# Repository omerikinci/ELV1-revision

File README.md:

# ELV1 Revision

Standalone KiCad hardware repository for the ELV1 revision project.

Main project file:

```text
hardware/ELV1-revision/ELV1 revision.kicad_pro
```

Local project libraries are kept under:

```text
hardware/libraries
```

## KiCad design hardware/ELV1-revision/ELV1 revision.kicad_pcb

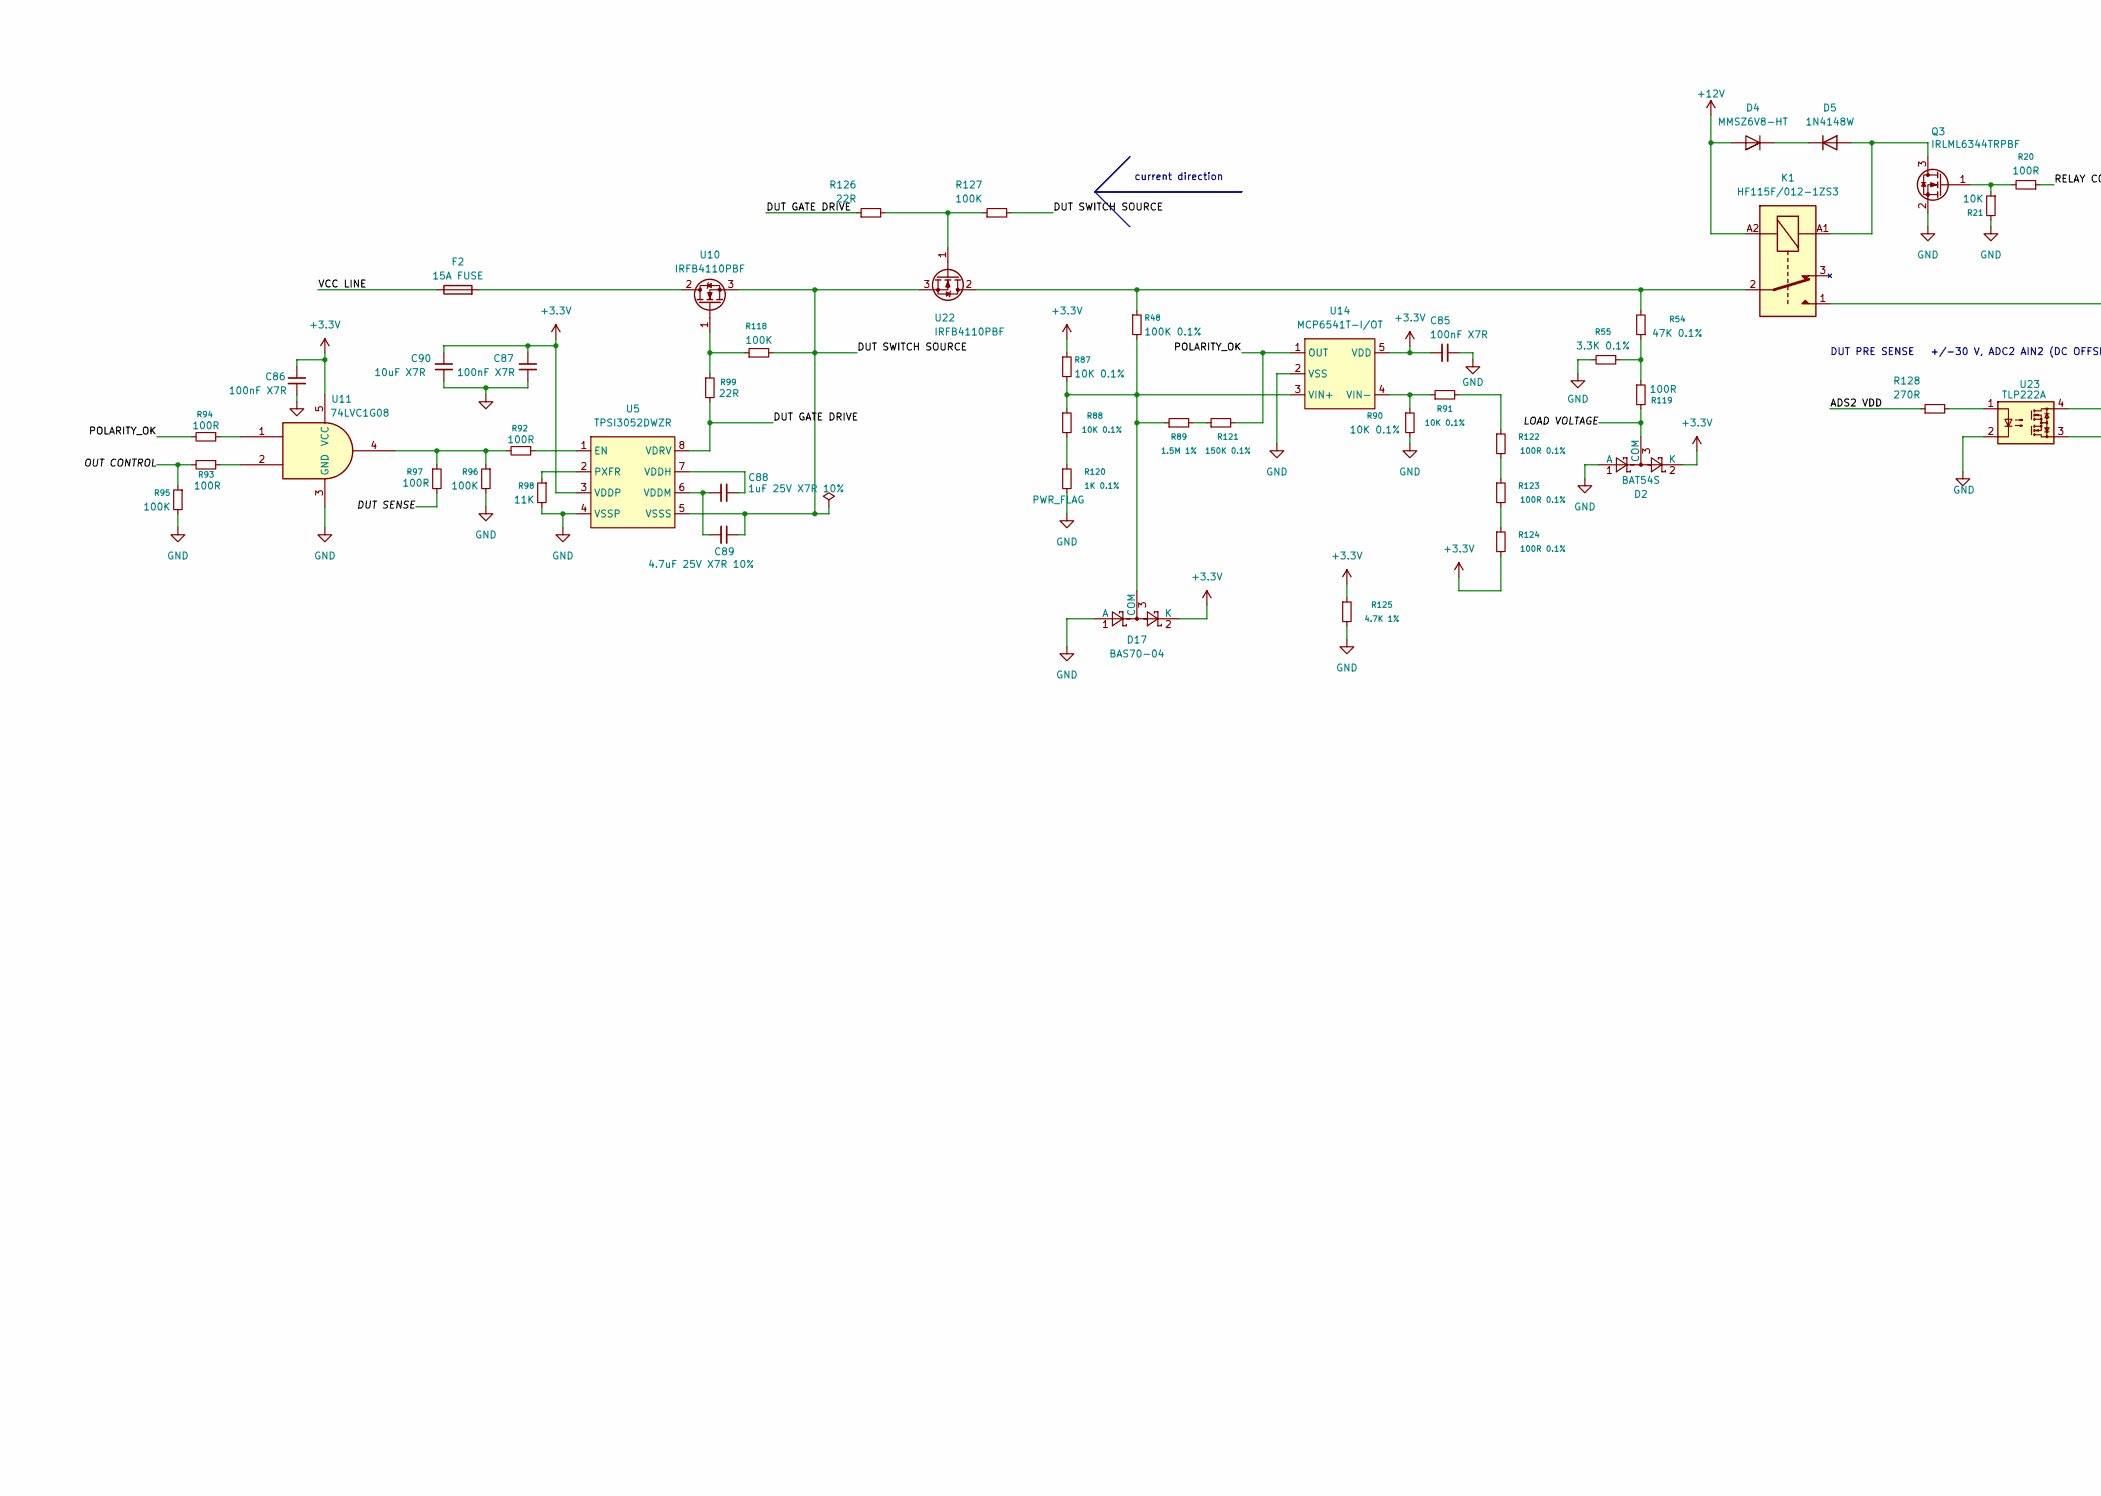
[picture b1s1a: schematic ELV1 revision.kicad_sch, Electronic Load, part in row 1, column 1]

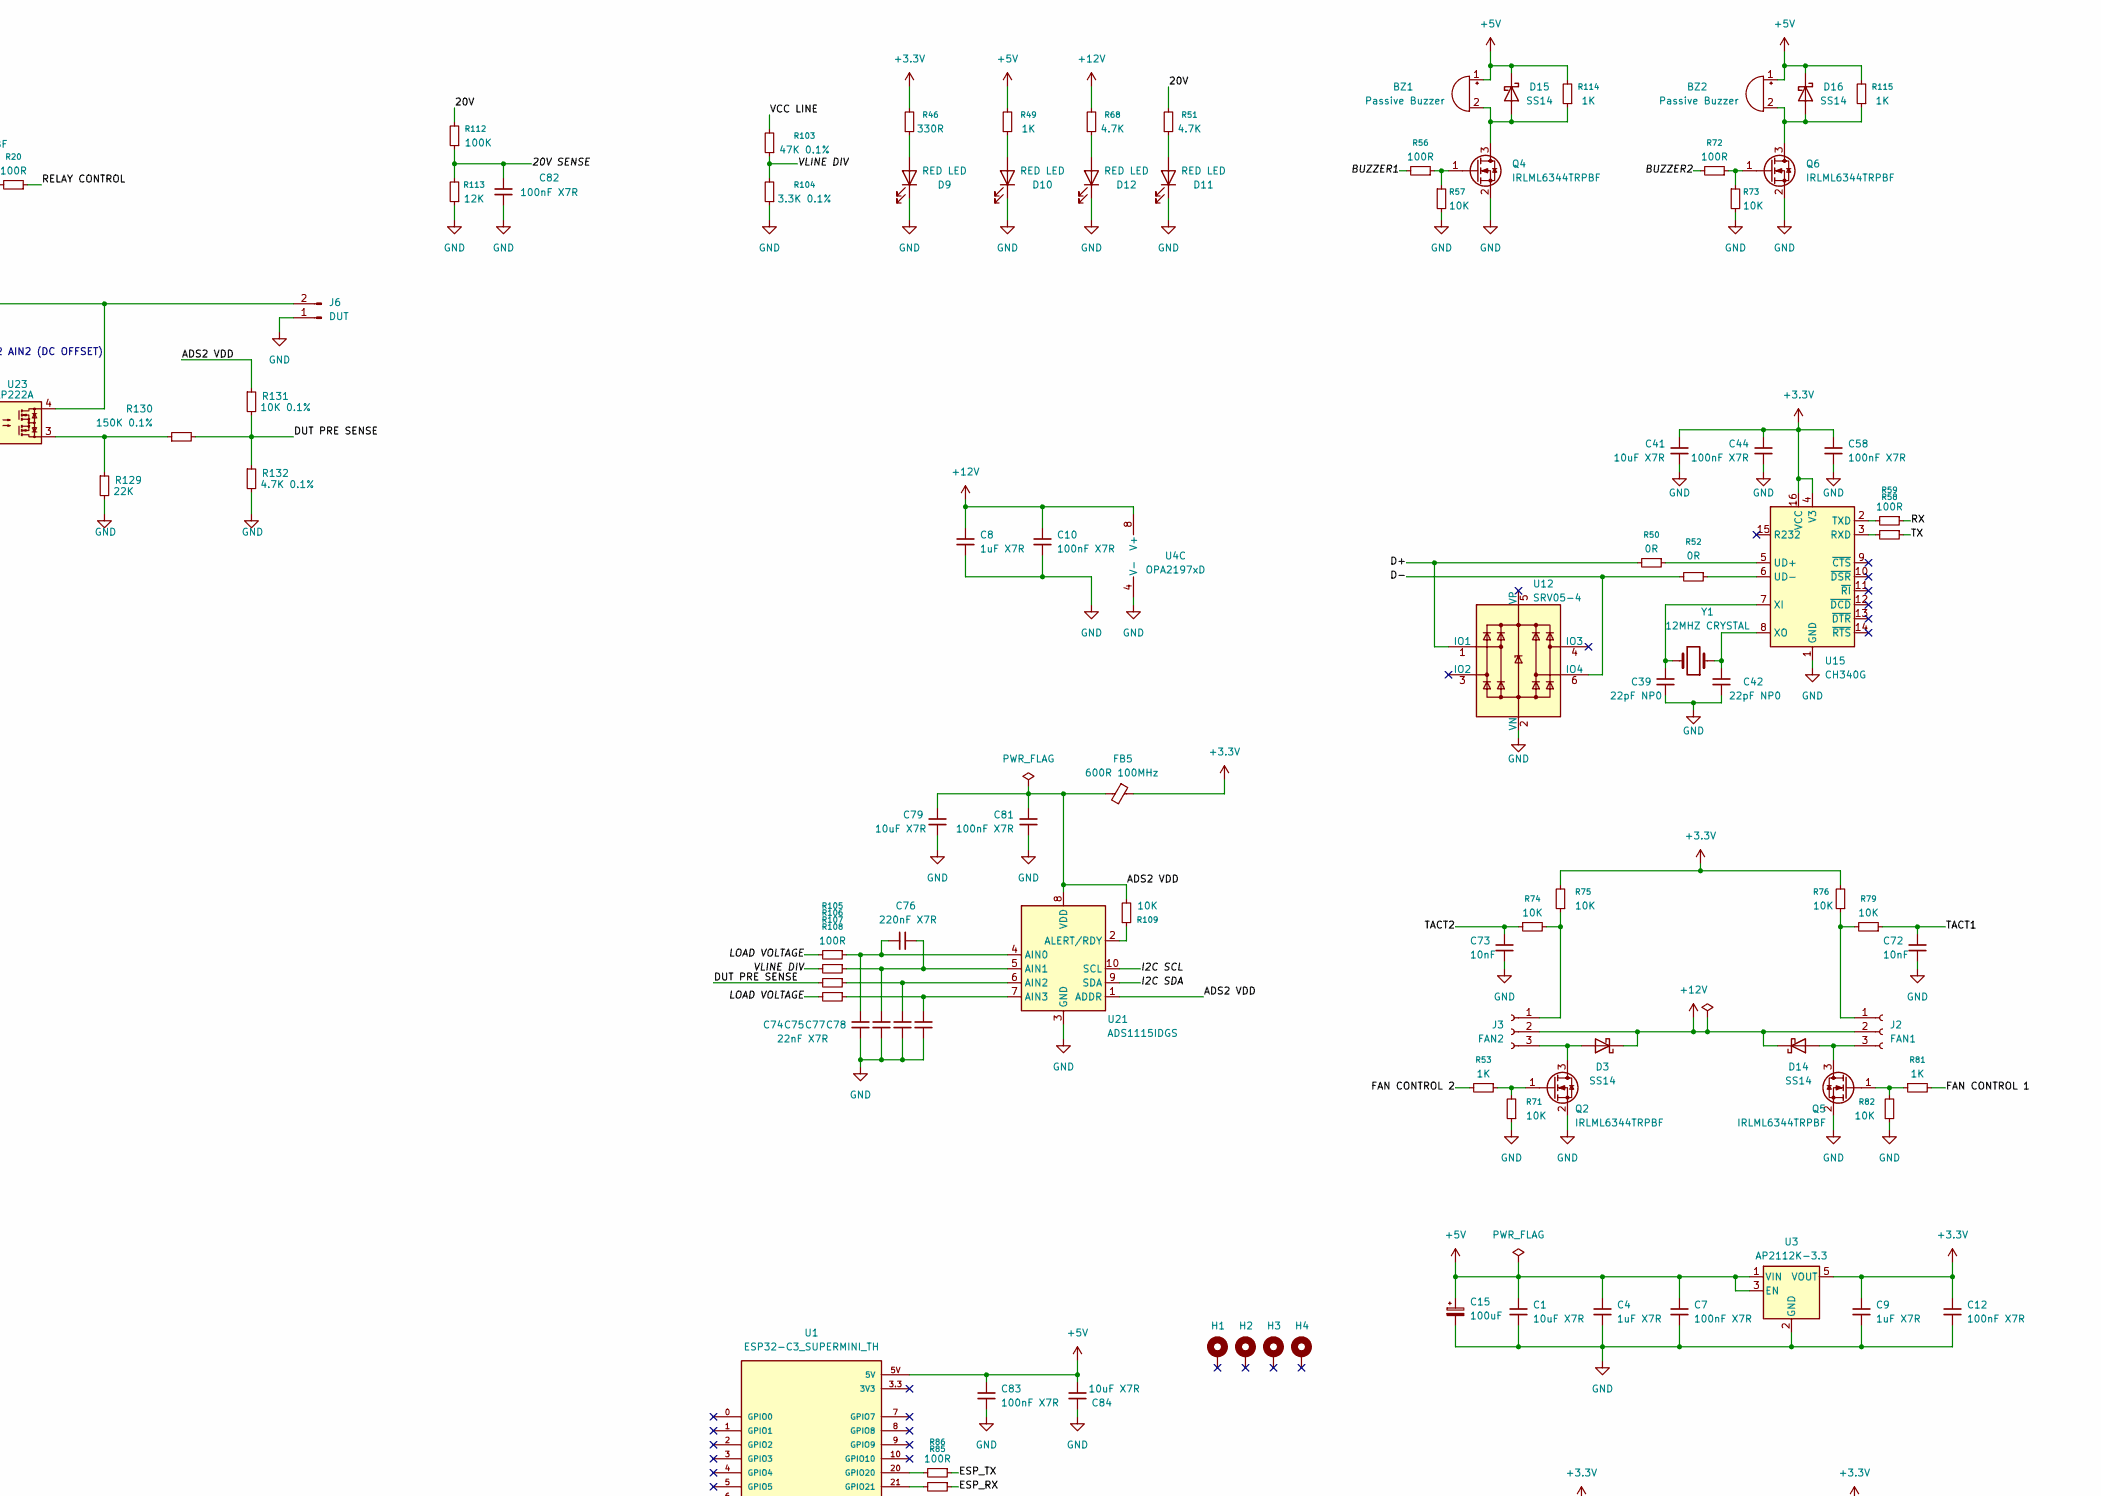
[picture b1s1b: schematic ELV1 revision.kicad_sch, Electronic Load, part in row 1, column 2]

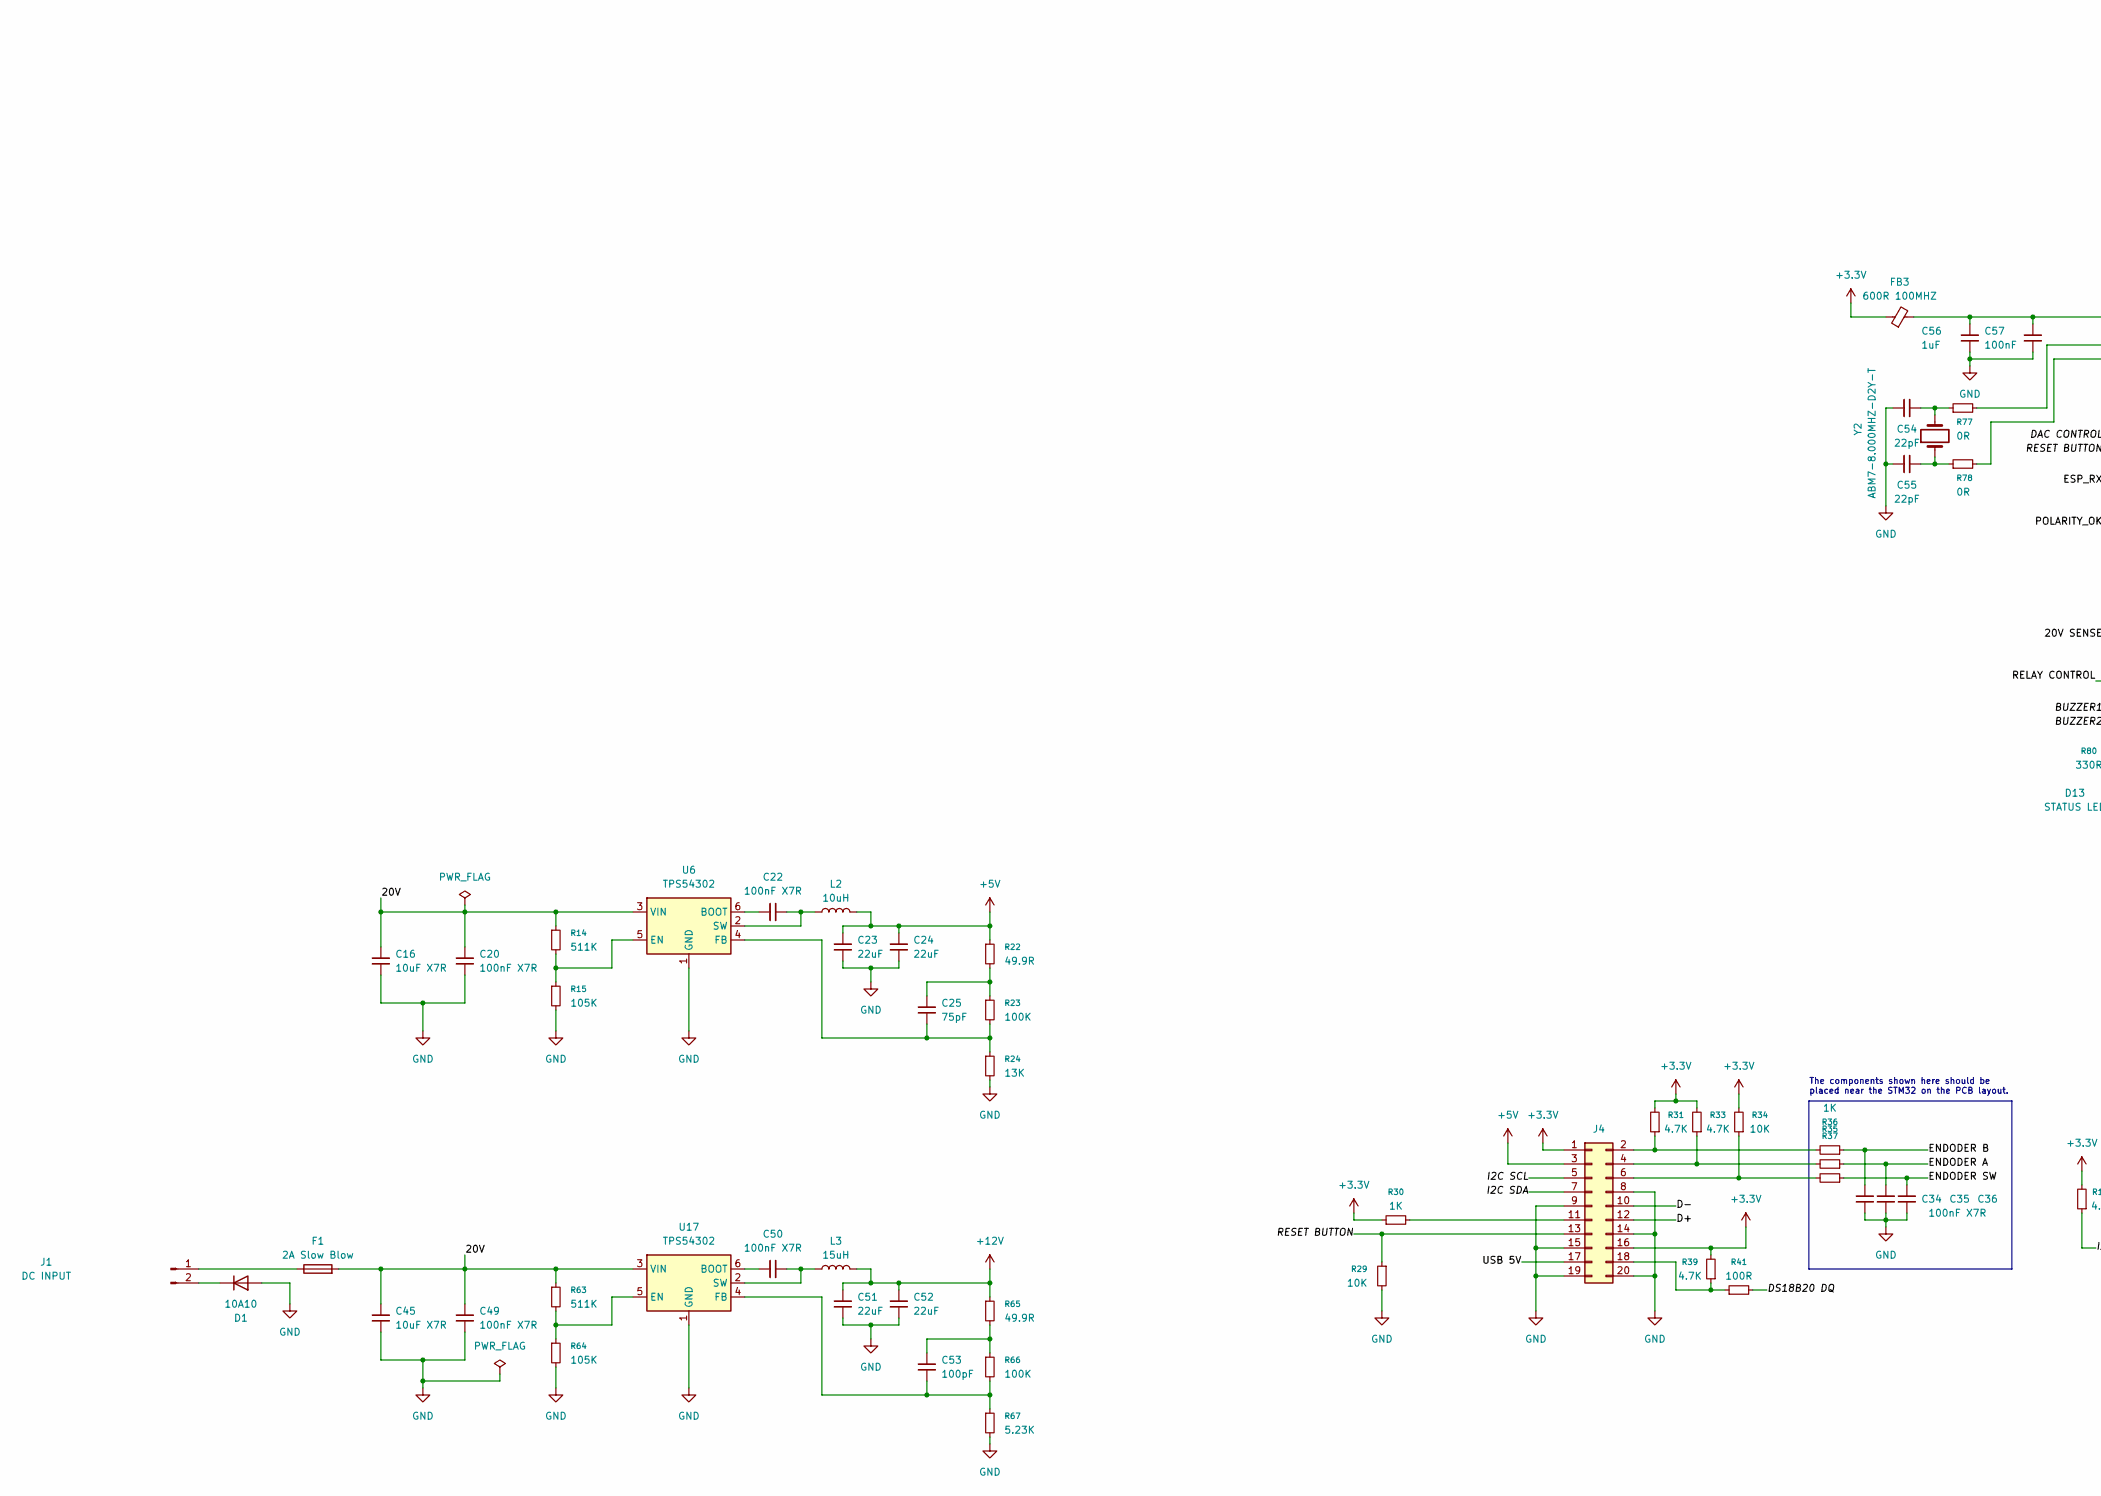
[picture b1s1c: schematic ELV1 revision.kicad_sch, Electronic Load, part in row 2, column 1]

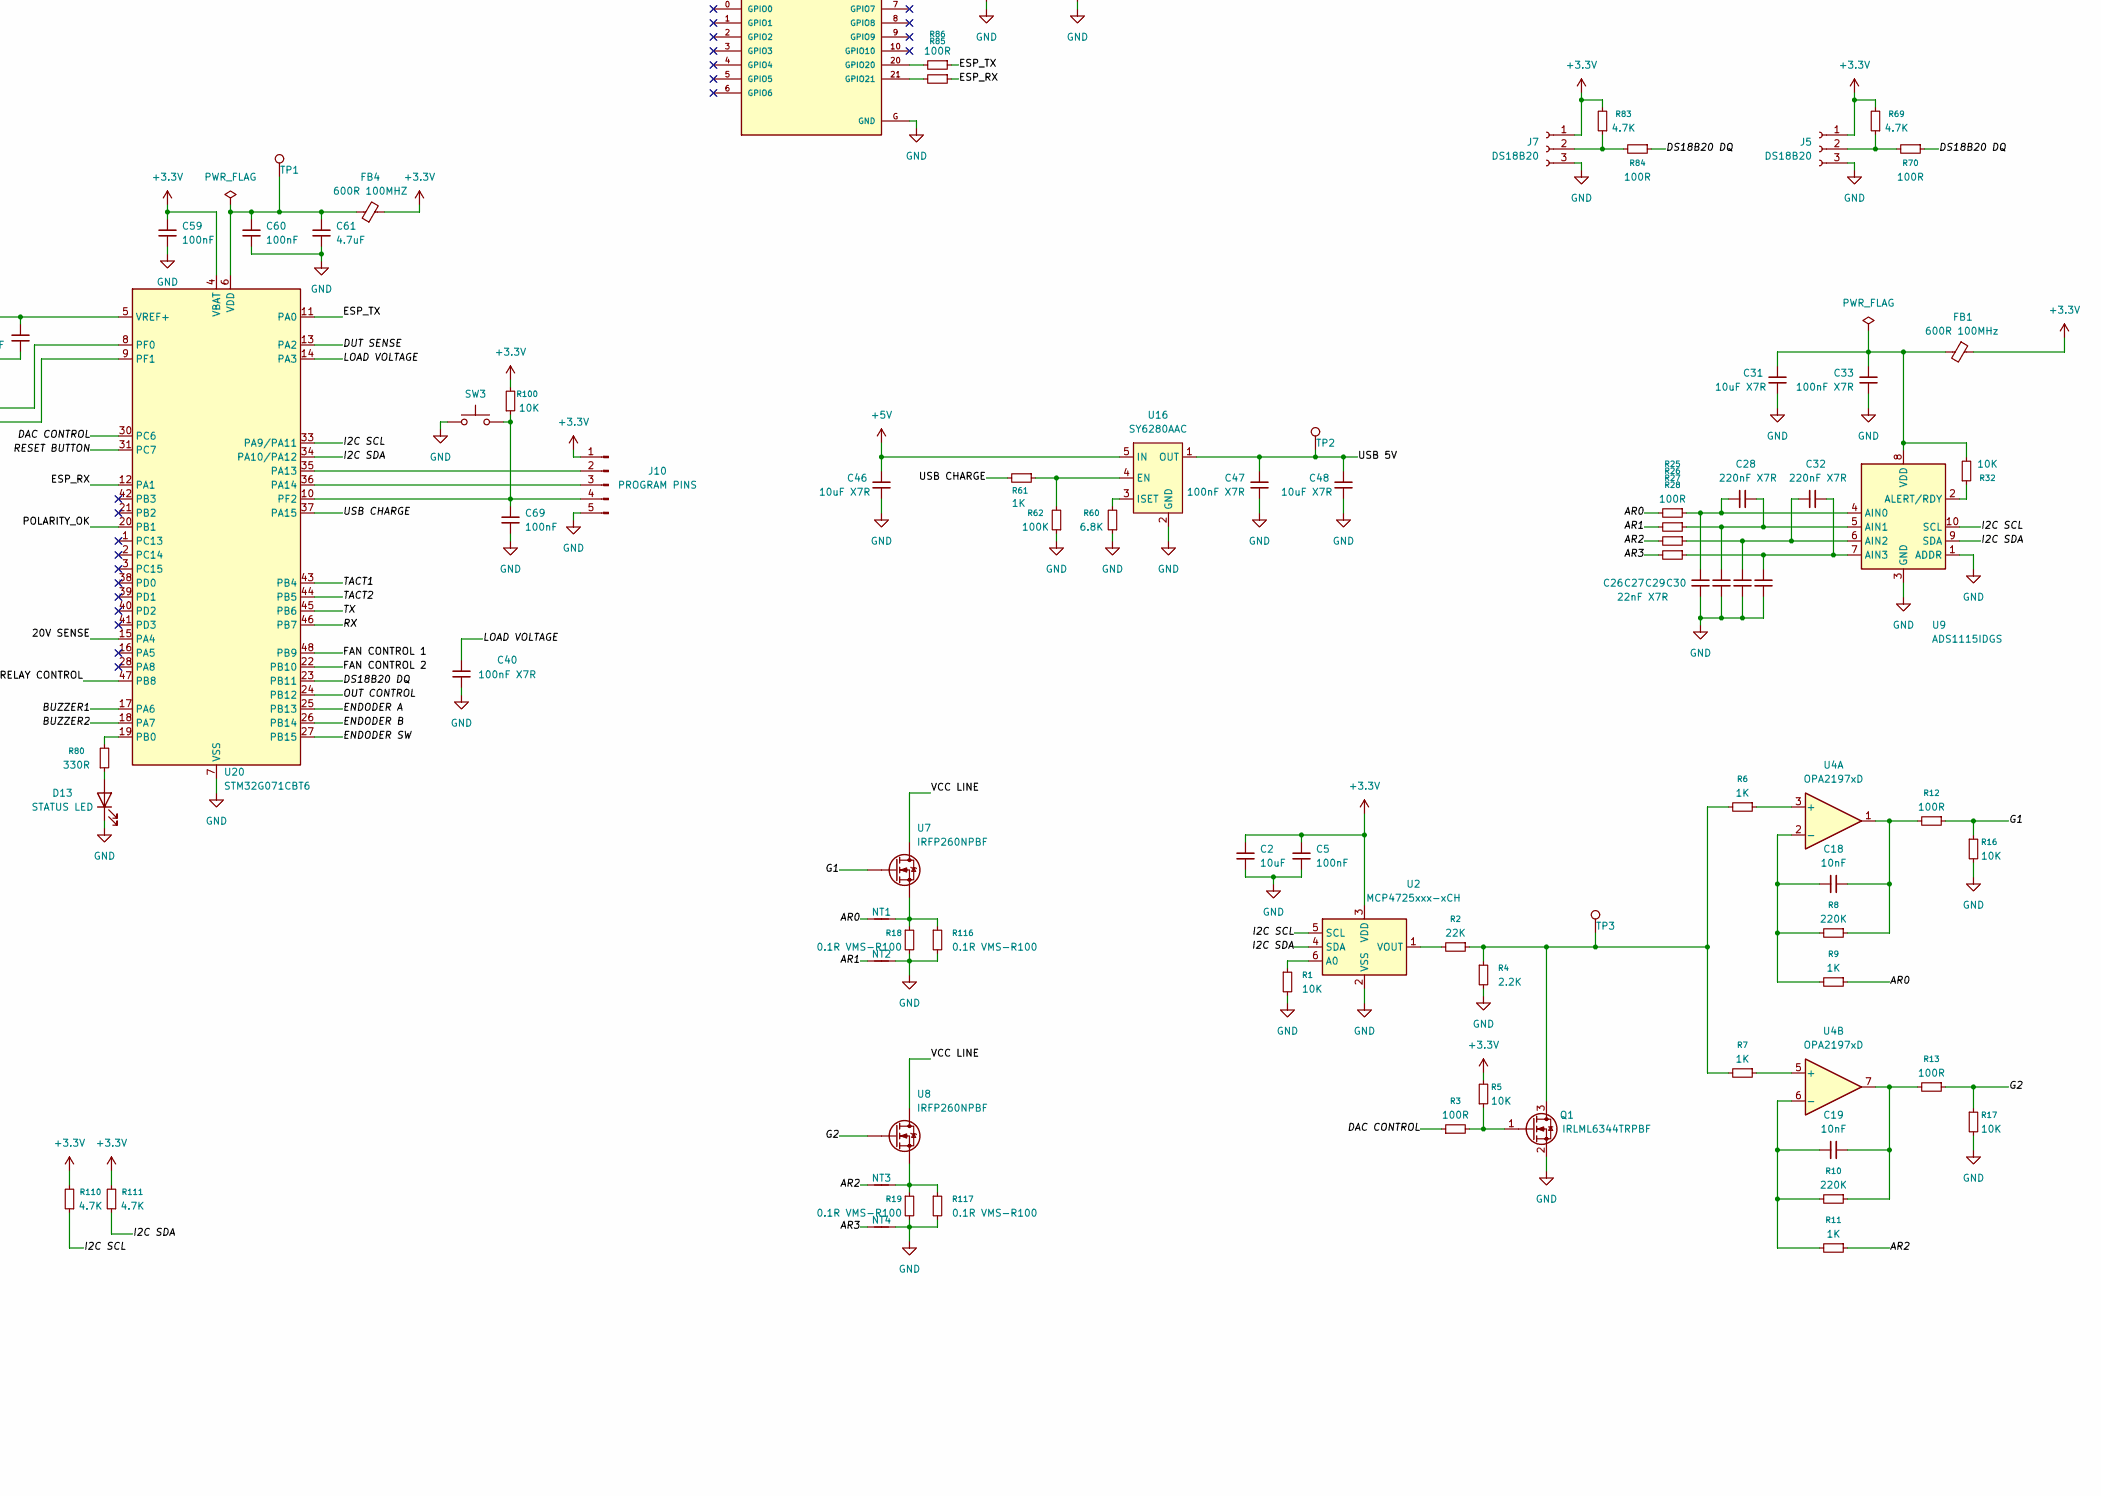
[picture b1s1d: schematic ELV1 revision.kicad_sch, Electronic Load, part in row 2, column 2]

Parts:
BZ1, BZ2: Passive Buzzer; Buzzer_15x7.5RM7.6
C1, C16, C31, C41, C45, C46, C48, C79, C84, C90: 10uF X7R; C_0805_2012Metric
C2: 10uF; C_0805_2012Metric
C4, C8, C9: 1uF X7R; C_0805_2012Metric
C5, C57, C59, C60, C69: 100nF; C_0805_2012Metric
C7, C10, C12, C20, C22, C33, C34, C35, C36, C40, C44, C47, C49, C50, C58, C81, C82, C83, C85, C86, C87: 100nF X7R; C_0805_2012Metric
C15: 100uF; CP_Radial_D6.3mm_P2.50mm
C18, C19, C72, C73: 10nF; C_0805_2012Metric
C23, C24, C51, C52: 22uF; C_0805_2012Metric
C25: 75pF; C_0805_2012Metric
C26, C27, C29, C30, C74, C75, C77, C78: 22nF X7R; C_0805_2012Metric
C28, C32, C76: 220nF X7R; C_0805_2012Metric
C39, C42: 22pF NP0; C_0805_2012Metric
C53: 100pF; C_0805_2012Metric
C54, C55: 22pF; C_0805_2012Metric
C56: 1uF; C_0805_2012Metric
C61: 4.7uF; C_0805_2012Metric
C88: 1uF 25V X7R 10%; C_0805_2012Metric; MPN CL21B105KAFNNNE
C89: 4.7uF 25V X7R 10%; C_1206_3216Metric; MPN CL31B475KAHNNNE
D1: 10A10; D_P600_R-6_P7.62mm_Vertical_CathodeUp
D2: BAT54S; SOT-23-3
D3, D14, D15, D16: SS14; D_SMA
D4: MMSZ6V8-HT; D_SOD-123
D5: 1N4148W; D_SOD-123
D9, D10, D11, D12: RED LED; LED_0805_2012Metric_Pad1.15x1.40mm_HandSolder
D13: STATUS LED; LED_0805_2012Metric
D17: BAS70-04; SOT-23-3; MPN BAS70-04,215
F1: 2A Slow Blow; Fuse_Littelfuse_395Series
F2: 15A FUSE; Fuseholder_Clip-5x20mm_Keystone_3512_Inline_P23.62x7.27mm_D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
FB1, FB5: 600R 100MHz; L_0603_1608Metric_Pad1.05x0.95mm_HandSolder
FB3, FB4: 600R 100MHZ; L_0603_1608Metric
H1, H2, H3, H4: MountingHole_Pad; MountingHole_3.2mm_M3_Pad_Via
J1: DC INPUT; PhoenixContact_MSTBVA_2,5_2-G-5,08_1x02_P5.08mm_Vertical
J2: FAN1; Molex_Micro-Latch_53253-0370_1x03_P2.00mm_Vertical
J3: FAN2; Molex_Micro-Latch_53253-0370_1x03_P2.00mm_Vertical
J4: Conn_02x10_Odd_Even; JST_PUD_B20B-PUDSS_2x10_P2.00mm_Vertical
J5, J7: DS18B20; Molex_Micro-Latch_53253-0370_1x03_P2.00mm_Vertical
J6: DUT; AMASS_XT60-M_1x02_P7.20mm_Vertical
J10: PROGRAM PINS; PinHeader_1x05_P2.54mm_Vertical
K1: HF115F/012-1ZS3; Relay_SPDT_Hongfa_HF115F-1Z-x3
L2: 10uH; L_7.3x7.3_H4.5
L3: 15uH; L_SOREDE_SNR.1050_10x10x5mm
NT1, NT2, NT3, NT4: NetTie_2; NetTie-2_SMD_Pad0.5mm
Q1, Q2, Q3, Q5: IRLML6344TRPBF; SOT-23
Q4, Q6: IRLML6344TRPBF; SOT-23-3
R1, R5, R16, R17, R21, R29, R32, R34, R57, R71, R73, R74, R75, R76, R79, R82, R100, R109: 10K; R_0805_2012Metric
R2, R129: 22K; R_0805_2012Metric
R3, R12, R13, R20, R25, R26, R27, R28, R41, R56, R58, R59, R70, R72, R84, R85, R86, R92, R93, R94, R97, R105, R106, R107, R108, R119: 100R; R_0805_2012Metric
R4: 2.2K; R_0805_2012Metric
R6, R7, R9, R11, R30, R35, R36, R37, R49, R53, R61, R81, R114, R115: 1K; R_0805_2012Metric
R8, R10: 220K; R_0805_2012Metric
R14, R63: 511K; R_0805_2012Metric
R15, R64: 105K; R_0805_2012Metric
R18, R19, R116, R117: 0.1R VMS-R100; R_2512_6332Metric_Pad1.40x3.35mm_HandSolder
R22, R65: 49.9R; R_0805_2012Metric
R23, R62, R66, R95, R96, R112, R118, R127: 100K; R_0805_2012Metric
R24: 13K; R_0805_2012Metric
R31, R33, R39, R51, R68, R69, R83, R110, R111: 4.7K; R_0805_2012Metric
R46, R80: 330R; R_0805_2012Metric
R48: 100K 0.1%; R_0805_2012Metric
R50, R52: 0R; R_0805_2012Metric
R54, R103: 47K 0.1%; R_0805_2012Metric
R55, R104: 3.3K 0.1%; R_0805_2012Metric
R60: 6.8K; R_0805_2012Metric
R67: 5.23K; R_0805_2012Metric
R77, R78: 0R; R_0603_1608Metric
R87, R88, R90, R91, R131: 10K 0.1%; R_0805_2012Metric
R89: 1.5M 1%; R_0805_2012Metric
R98: 11K; R_0805_2012Metric
R99, R126: 22R; R_0805_2012Metric
R113: 12K; R_0805_2012Metric
R120: 1K 0.1%; R_0805_2012Metric
R121, R130: 150K 0.1%; R_0805_2012Metric
R122, R123, R124: 100R 0.1%; R_0805_2012Metric
R125: 4.7K 1%; R_0805_2012Metric
R128: 270R; R_0805_2012Metric
R132: 4.7K 0.1%; R_0805_2012Metric
SW3: SW_Push; SW_Push_1P1T_XKB_TS-1187A
TP1, TP3: TestPoint; TestPoint_Pad_2.0x2.0mm
TP2: TestPoint; TestPoint_Pad_1.0x1.0mm
U1: ESP32-C3_SUPERMINI_TH; MODULE_ESP32-C3_SUPERMINI_TH; MPN ESP32-C3 SuperMini_TH
U2: MCP4725xxx-xCH; SOT-23-6
U3: AP2112K-3.3; SOT-23-5
U4: OPA2197xD; SOIC-8_3.9x4.9mm_P1.27mm
U5: TPSI3052DWZR; SOIC-8_7.5x5.85mm_P1.27mm
U6, U17: TPS54302; SOT-23-6
U7, U8: IRFP260NPBF; TO-247 Edge Castellated
U9, U21: ADS1115IDGS; TSSOP-10_3x3mm_P0.5mm
U10, U22: IRFB4110PBF; Untitled
U11: 74LVC1G08; Texas_R-PDSO-G5_DCK-5
U12: SRV05-4; SOT-23-6
U14: MCP6541T-I/OT; SOT-23-5
U15: CH340G; SOIC-16_3.9x9.9mm_P1.27mm
U16: SY6280AAC; SOT-23-5_HandSoldering
U20: STM32G071CBT6; LQFP-48_7x7mm_P0.5mm
U23: TLP222A; DIP-4_W7.62mm
Y1: 12MHZ CRYSTAL; Crystal_SMD_HC49-SD
Y2: ABM7-8.000MHZ-D2Y-T; Crystal_SMD_Abracon_ABM7-2Pin_6.0x3.5mm

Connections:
+3.3V: C2.1, C5.1, C9.1, C12.1, C41.1, C44.1, C58.1, C59.1, C85.1, C86.2, C87.2, C90.2, D2.2 (K), D17.2 (K), FB1.1, FB3.1, FB4.2, FB5.1, J4.1, J4.16, J5.1, J7.1, J10.1, R5.2, R30.1, R31.2, R33.2, R34.2, R39.2, R46.2, R69.2, R75.2, R76.2, R83.2, R87.1, R100.2, R110.2, R111.2, R124.2, R125.1, U2.3 (VDD), U3.5 (VOUT), U5.3 (VDDP), U11.5 (VCC), U14.5 (VDD), U15.4 (V3), U15.16 (VCC), U20.4 (VBAT); also elsewhere on the board
+5V: BZ1.1 (+), BZ2.1 (+), C1.1, C4.1, C7.1, C15.1, C23.1, C24.1, C46.1, C83.1, C84.2, D15.1 (K), D16.1 (K), J4.3, L2.2, R22.1, R49.2, R114.2, R115.2, U1.5V, U3.1 (VIN), U3.3 (EN), U16.5 (IN)
+12V: C8.1, C10.1, C51.1, C52.1, D3.1 (K), D4.2 (+), D14.1 (K), J2.2, J3.2, K1.A2, L3.2, R65.1, R68.2, U4.8 (V+); also elsewhere on the board
/20V SENSE: C82.1, R112.1, R113.2, U20.15 (PA4)
/ADS2 VDD: C79.1, C81.1, FB5.2, R109.2, R128.1, R131.1, U21.1 (ADDR), U21.8 (VDD)
/AR0: NT1.1, R9.1, R25.2
/AR1: NT2.1, R26.2
/AR2: NT3.1, R11.1, R27.2
/AR3: NT4.1, R28.2
/BUZZER1: R56.2, U20.17 (PA6)
/BUZZER2: R72.2, U20.18 (PA7)
/D+: J4.12, R50.2, U12.1 (IO1)
/D-: J4.10, R52.2, U12.6 (IO4)
/DAC CONTROL: R3.1, U20.30 (PC6)
/DS18B20 DQ: R41.2, R70.1, R84.1, U20.23 (PB11)
/DUT SENSE: R97.2, U20.13 (PA2)
/ENDODER A: C35.1, R36.1, U20.25 (PB13)
/ENDODER B: C34.1, R35.1, U20.26 (PB14)
/ENDODER SW: C36.1, R37.1, U20.27 (PB15)
/ESP_RX: R86.1, U20.12 (PA1)
/ESP_TX: R85.1, U20.11 (PA0)
/FAN CONTROL 1: R81.2, U20.48 (PB9)
/FAN CONTROL 2: R53.2, U20.22 (PB10)
/G1: R12.1, R16.1, U7.1 (G)
/G2: R13.1, R17.1, U8.1 (G)
/I2C SCL: J4.5, R110.1, U2.5 (SCL), U9.10 (SCL), U20.33 (PA9/PA11), U21.10 (SCL)
/I2C SDA: J4.7, R111.1, U2.4 (SDA), U9.9 (SDA), U20.34 (PA10/PA12), U21.9 (SDA)
/LOAD VOLTAGE: C40.1, D2.3 (COM), R105.2, R108.2, R119.2, U20.14 (PA3)
/OUT CONTROL: R93.2, R95.1, U20.24 (PB12); also elsewhere on the board
/POLARITY_OK: R94.2, R121.2, U14.1 (OUT), U20.20 (PB1)
/RELAY CONTROL: R20.1, U20.47 (PB8)
/RESET BUTTON: J4.13, R29.1, U20.31 (PC7)
/RX: R58.1, U20.46 (PB7)
/TACT1: C72.1, R79.1, U20.43 (PB4)
/TACT2: C73.1, R74.1, U20.44 (PB5)
/TX: R59.1, U20.45 (PB6)
/USB 5V: C47.1, C48.1, J4.17, TP2.1 (1_1), U16.1 (OUT)
/USB CHARGE: R61.2, U20.37 (PA15)
/VCC LINE: F2.1, R103.2, U7.2 (D), U8.2 (D)
/VLINE DIV: R103.1, R104.2, R106.2
unnamed: BZ1.2 (-), D15.2 (A), Q4.3 (D), R114.1
unnamed: BZ2.2 (-), D16.2 (A), Q6.3 (D), R115.1
unnamed: C18.2, R8.1, R12.2, U4.1
unnamed: C19.2, R10.1, R13.2, U4.7
unnamed: C25.1, R22.2, R23.1
unnamed: C53.1, R65.2, R66.1
unnamed: C54.2, R77.1, Y2.2
unnamed: C55.2, R78.1, Y2.1
unnamed 51: D1.3; also elsewhere on the board
unnamed: D3.2 (A), J3.3, Q2.3 (D)
unnamed: D9.2 (A), R46.1
unnamed: D10.2 (A), R49.1
unnamed: D11.2 (A), R51.1
unnamed: D12.2 (A), R68.1
unnamed: D13.2 (A), R80.1
unnamed: D14.2 (A), J2.3, Q5.3 (D)
unnamed: D17.3 (COM), R48.2, R87.2, R88.1, R89.1, U14.3 (VIN+)
unnamed: F1.1, J1.1
unnamed: J2.1, R76.1, R79.2
unnamed: J3.1, R74.2, R75.1
unnamed: J4.2, R31.1, R35.2
unnamed: J4.4, R33.1, R36.2
unnamed: J4.6, R34.1, R37.2
unnamed: J4.11, R30.2
unnamed: J4.18, R39.1, R41.1
unnamed: J5.2, R69.1, R70.2
unnamed 73: J6.2, K1.1, U23.4; also elsewhere on the board
unnamed: J7.2, R83.1, R84.2
unnamed: J10.2, U20.35 (PA13)
unnamed: J10.3, U20.36 (PA14)
unnamed: C69.1, J10.4, R100.1, SW3.2, U20.10 (PF2)
unnamed: Q1.3 (D), R2.1, R4.1, R6.2, R7.2, TP3.1 (1_1)
unnamed: Q1.1 (G), R3.2, R5.1
unnamed: Q2.1 (G), R53.1, R71.2
unnamed 97: Q3.1 (G), R20.2, R21.1; also elsewhere on the board
unnamed: Q4.1 (G), R56.1, R57.1
unnamed: Q5.1 (G), R81.1, R82.2
unnamed: Q6.1 (G), R72.1, R73.1
unnamed: R92.2, R96.1, R97.1, U11.4
unnamed: R93.1, U11.2
unnamed: R94.1, U11.1
unnamed: R54.1, R55.1, R119.1
unnamed: R88.2, R120.1
unnamed: R89.2, R121.1
unnamed: R91.2, R122.1
unnamed: R122.2, R123.1
unnamed: R123.2, R124.1
unnamed: R126.2, R127.1, U22.1 (G)
unnamed: R128.2, U23.1
unnamed: R129.1, R130.1, U23.3
unnamed: R85.2, U1.20 (GPIO20)
unnamed: R86.2, U1.21 (GPIO21)
unnamed: R1.1, U2.6 (A0)
unnamed: R2.2, U2.1 (VOUT)
unnamed: R6.1, U4.3 (+)
unnamed: C18.1, R8.2, R9.2, U4.2 (-)
unnamed: R7.1, U4.5 (+)
unnamed: C19.1, R10.2, R11.2, U4.6 (-)
unnamed: R92.1, U5.1 (EN)
unnamed: R98.1, U5.2 (PXFR)
unnamed: C88.1, U5.7 (VDDH)
unnamed: C88.2, C89.2, U5.6 (VDDM)
unnamed: R99.2, R126.1, U5.8 (VDRV)
unnamed: C22.1, U6.6 (BOOT)
unnamed: R14.2, R15.1, U6.5 (EN)
unnamed: C25.2, R23.2, R24.1, U6.4 (FB)
unnamed: C22.2, L2.1, U6.2 (SW)
unnamed: NT1.2, R18.1, R116.1, U7.3 (S)
unnamed: NT3.2, R19.1, R117.1, U8.3 (S)
unnamed: C26.1, C28.2, R25.1, U9.4 (AIN0)
unnamed: C27.1, C28.1, R26.1, U9.5 (AIN1)
unnamed: C29.1, C32.2, R27.1, U9.6 (AIN2)
unnamed: C30.1, C32.1, R28.1, U9.7 (AIN3)
unnamed: R32.1, U9.2 (ALERT/RDY)
unnamed: C31.1, C33.1, FB1.2, R32.2, U9.8 (VDD)
unnamed: F2.2, U10.2 (D)
unnamed: R99.1, R118.1, U10.1 (G)
unnamed: R90.1, R91.1, U14.4 (VIN-)
unnamed: R59.2, U15.3 (RXD)
unnamed: R58.2, U15.2 (TXD)
unnamed: R50.1, U15.5 (UD+)
unnamed: R52.1, U15.6 (UD-)
unnamed: C39.1, U15.7 (XI), Y1.2
unnamed: C42.1, U15.8 (XO), Y1.1
unnamed: R61.1, R62.2, U16.4 (EN)
unnamed: R60.2, U16.3 (ISET)
unnamed: C50.1, U17.6 (BOOT)
unnamed: R63.2, R64.1, U17.5 (EN)
unnamed: C53.2, R66.2, R67.1, U17.4 (FB)
unnamed: C50.2, L3.1, U17.2 (SW)
unnamed: R80.2, U20.19 (PB0)
unnamed: R77.2, U20.8 (PF0)
unnamed: R78.2, U20.9 (PF1)
unnamed: C60.1, C61.1, FB4.1, TP1.1 (1_1), U20.6 (VDD)
unnamed: C56.1, C57.1, FB3.2, U20.5 (VREF+)
unnamed: C74.1, C76.2, R105.1, U21.4 (AIN0)
unnamed: C75.1, C76.1, R106.1, U21.5 (AIN1)
unnamed 160: C77.1, R107.1, U21.6 (AIN2); also elsewhere on the board
unnamed 161: C78.1, R108.1, U21.7 (AIN3); also elsewhere on the board
unnamed: R109.1, U21.2 (ALERT/RDY)

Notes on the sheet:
The components shown here should be placed near the STM32 on the PCB layout.
DUT PRE SENSE +/-30 V, ADC2 AIN2 (DC OFFSET)
current direction

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
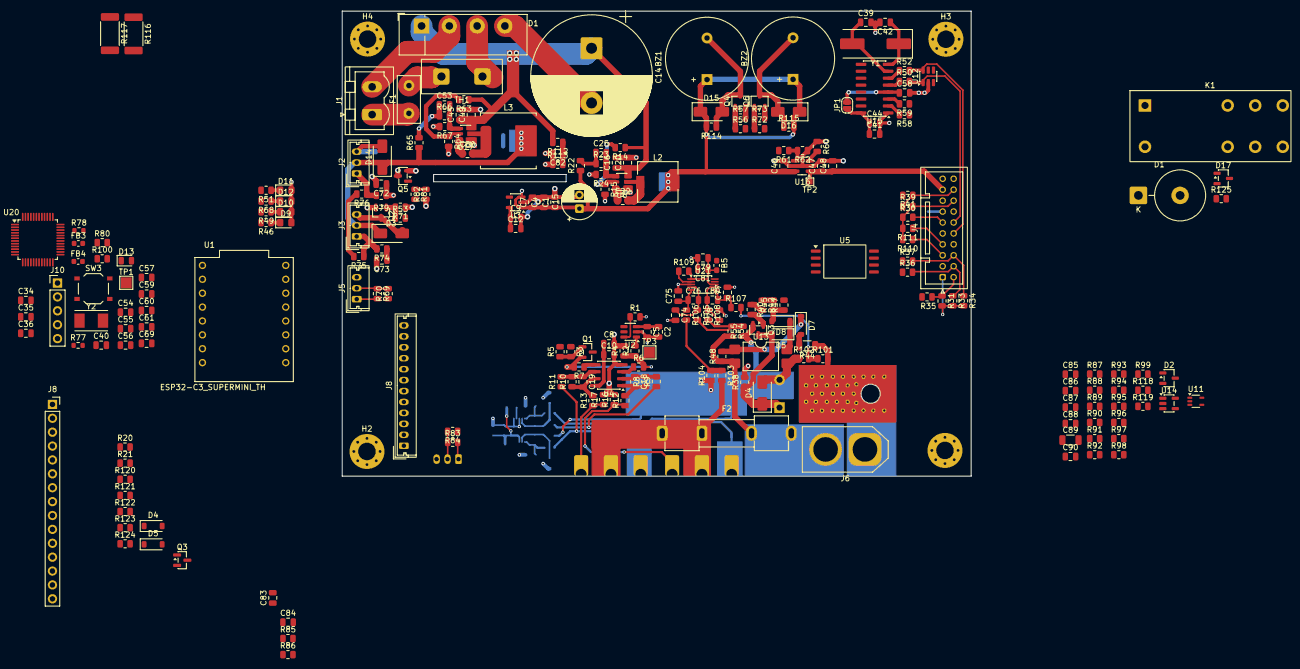
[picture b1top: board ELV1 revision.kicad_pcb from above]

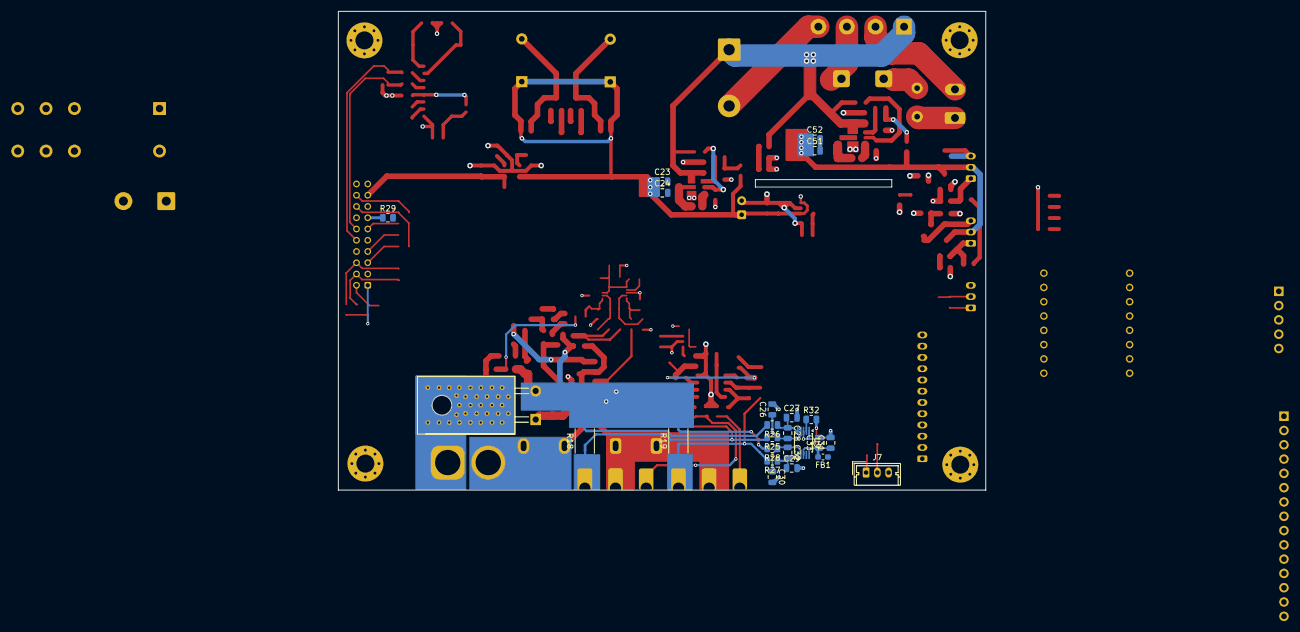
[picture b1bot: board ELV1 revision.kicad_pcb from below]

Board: 2 copper layers, 115.0 x 85.1 mm, 278 parts (28 on the bottom side), 150 nets.

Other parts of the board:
C14: 6800uF; CP_Radial_D22.0mm_P10.00mm_SnapIn
C80: 220nF X7R; C_0805_2012Metric
D1#2: 10A10; D_P600_R-6_P7.62mm_Vertical_CathodeUp
D4#2: 12V ZENER; D_SMA
D5#2, D7, D8: 1N4148W; D_SOD-123
J8: Conn_01x12_Socket; Molex_Micro-Latch_53253-1270_1x12_P2.00mm_Vertical
J8#2: EXTRA PIN; PinSocket_1x15_P2.54mm_Vertical
JP1: SolderJumper_2_Open; SolderJumper-2_P1.3mm_Open_RoundedPad1.0x1.5mm
Q3#2: IRLML6344TRPBF; SOT-23
R38: 100K; R_0805_2012Metric
R40: 100R; R_0805_2012Metric
R42: 10K; R_0805_2012Metric
R44: 5.6K; R_1206_3216Metric
R45: 47K; R_0805_2012Metric
R47: 100; R_0805_2012Metric
R101: 47K 0.1%; R_0805_2012Metric
R102: 3.3K 0.1%; R_0805_2012Metric
TH1: SCK13104MSY 10R; SCK13104MSY
U13: LTV-817S; SMDIP-4_W9.53mm

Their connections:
+3.3V: JP1.1 (A), R42.1, R45.2; also elsewhere on the board
+12V: R38.2; also elsewhere on the board
/OUT CONTROL: R40.1, R42.2; also elsewhere on the board
/VS-: R101.1, R102.2
GND1: R44.1, R101.2
unnamed 51: TH1.1; also elsewhere on the board
unnamed: D7.2 (A), R44.2
unnamed: D7.1 (K), U13.1
unnamed: D8.2 (A), R45.1, R47.1
unnamed 73: U13.2; also elsewhere on the board
unnamed 97: Q3#2.1 (G), R40.2; also elsewhere on the board
unnamed 160: C80.2; also elsewhere on the board
unnamed 161: C80.1; also elsewhere on the board
